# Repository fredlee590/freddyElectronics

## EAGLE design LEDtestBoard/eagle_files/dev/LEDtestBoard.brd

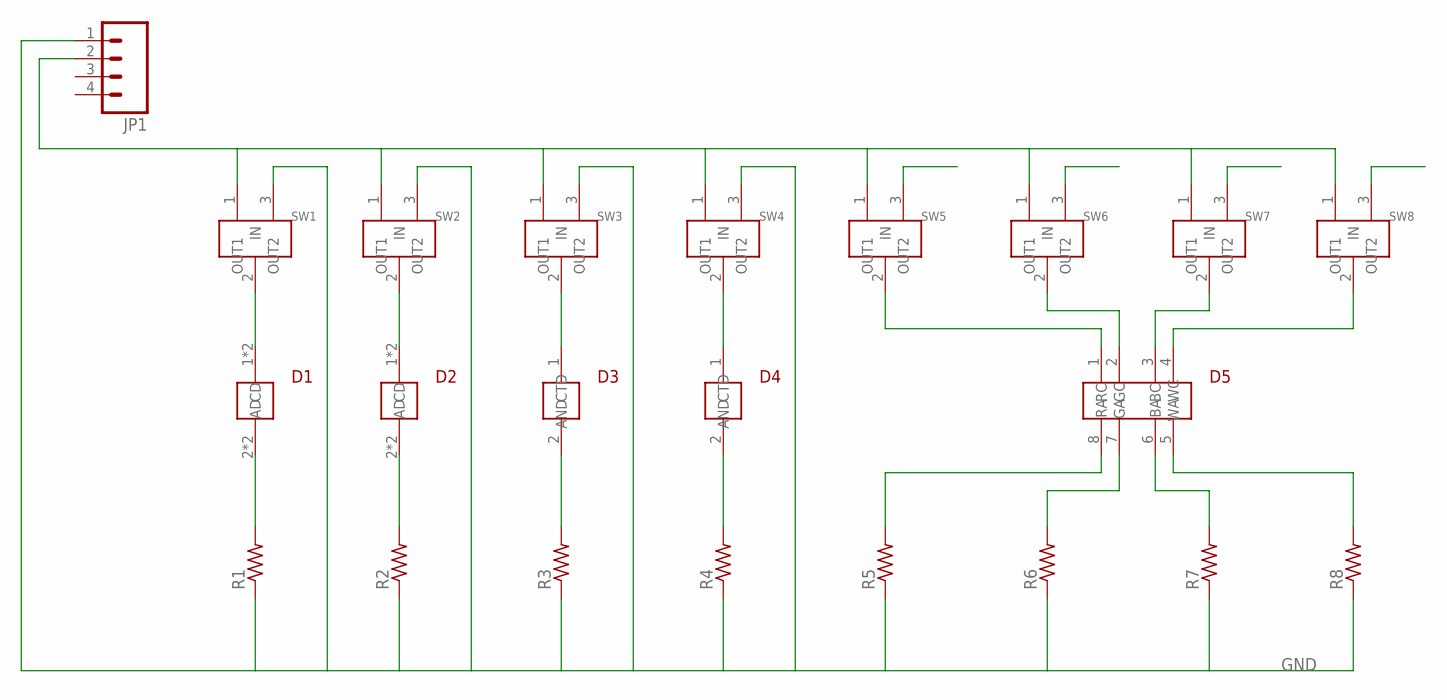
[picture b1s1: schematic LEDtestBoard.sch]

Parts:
D1, D2: SZA05A0A
D3, D4: LACN5MFBGB241Z; 2-SMD-LED-NO-EXP
D5: XLAMP_COLOR; 8-SMD-LED
JP1: M04PTH; 1X04
R1, R2, R3, R4, R5, R6, R7, R8: R-US_R0603; R0603
SW1, SW2, SW3, SW4, SW5, SW6, SW7, SW8: PCM12SMTR

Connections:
GND: JP1.1, R1.1, R2.1, R3.1, R4.1, R5.1, R6.1, R7.1, R8.1, SW1.3 (OUT2), SW2.3 (OUT2), SW3.3 (OUT2), SW4.3 (OUT2), SW5.3 (OUT2), SW6.3 (OUT2), SW7.3 (OUT2), SW8.3 (OUT2)
unnamed: JP1.2, SW1.1 (OUT1), SW2.1 (OUT1), SW3.1 (OUT1), SW4.1 (OUT1), SW5.1 (OUT1), SW6.1 (OUT1), SW7.1 (OUT1), SW8.1 (OUT1)
unnamed: D1.2 (CD), D1.12 (CD), R1.2
unnamed: D1.1 (AD), D1.11 (AD), SW1.2 (IN)
unnamed: D2.1 (AD), D2.11 (AD), SW2.2 (IN)
unnamed: D2.2 (CD), D2.12 (CD), R2.2
unnamed: D3.2 (CTD), R3.2
unnamed: D3.1 (AND), SW3.2 (IN)
unnamed: D4.1 (AND), SW4.2 (IN)
unnamed: D4.2 (CTD), R4.2
unnamed: D5.1 (RA), SW5.2 (IN)
unnamed: D5.2 (GA), SW6.2 (IN)
unnamed: D5.3 (BA), SW7.2 (IN)
unnamed: D5.4 (WA), SW8.2 (IN)
unnamed: D5.8 (RC), R5.2
unnamed: D5.7 (GC), R6.2
unnamed: D5.6 (BC), R7.2
unnamed: D5.5 (WC), R8.2

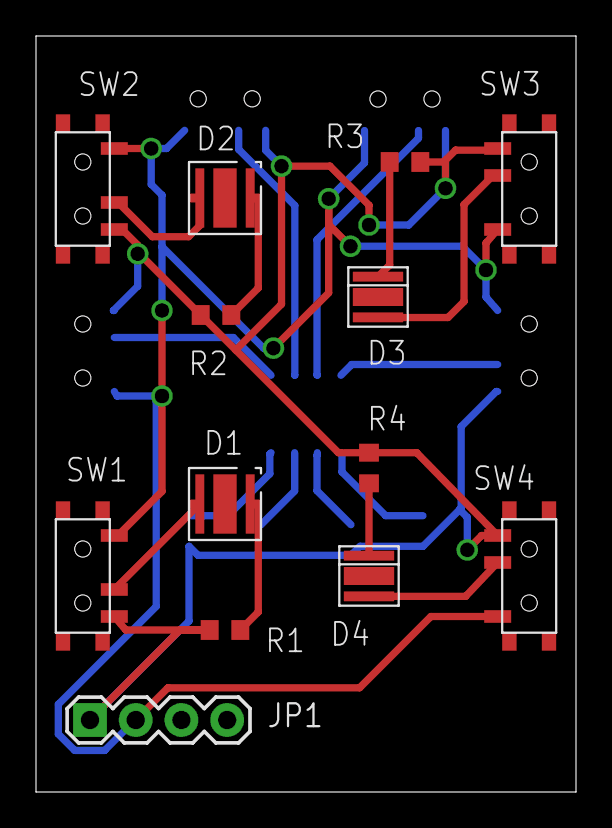
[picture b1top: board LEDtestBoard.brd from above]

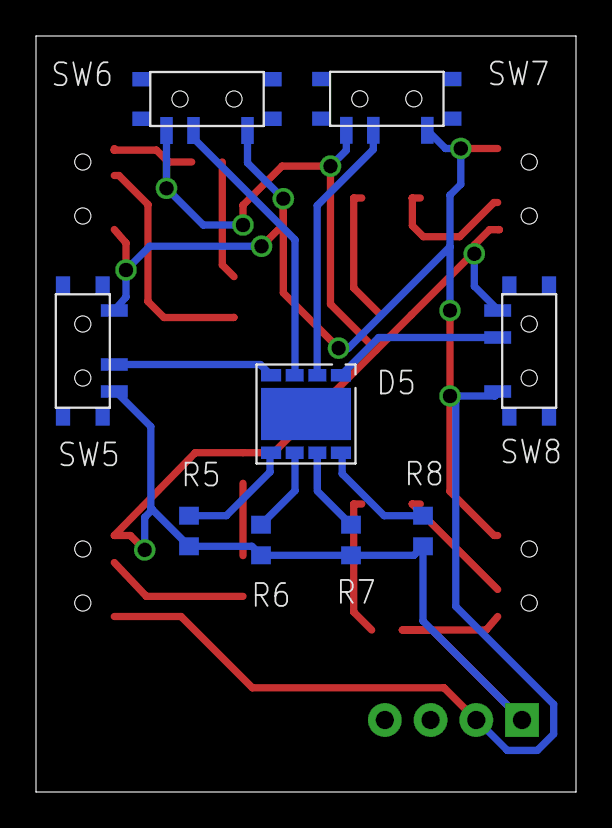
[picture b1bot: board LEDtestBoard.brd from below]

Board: 2 copper layers, 30.0 x 42.0 mm, 22 parts (9 on the bottom side), 18 nets.

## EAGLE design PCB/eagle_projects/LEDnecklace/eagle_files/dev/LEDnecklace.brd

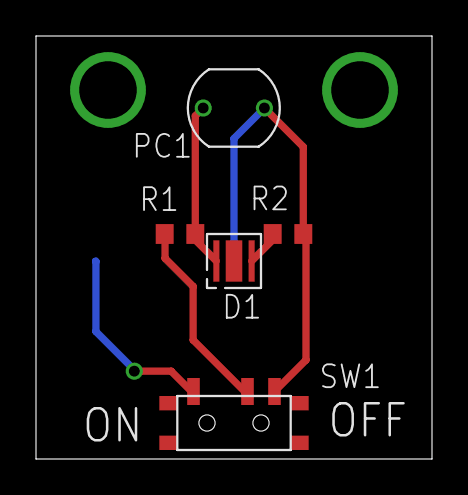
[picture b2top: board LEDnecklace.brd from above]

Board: 2 copper layers, 22.0 x 23.5 mm, 6 parts (1 on the bottom side), 5 nets.

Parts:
D1: XLAMP_XBD
P1: CR1220; CR1220/1225
PC1: PHOTOCELL_CERAMIC
R1, R2: R0603
SW1: PCM12SMTR

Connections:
unnamed: R1.2, SW1.2
unnamed: P1.GND, PC1.2, R2.1, SW1.3
unnamed: P1.VCC1, SW1.1
unnamed: D1.AD, PC1.1, R1.1
unnamed: D1.CD, R2.2

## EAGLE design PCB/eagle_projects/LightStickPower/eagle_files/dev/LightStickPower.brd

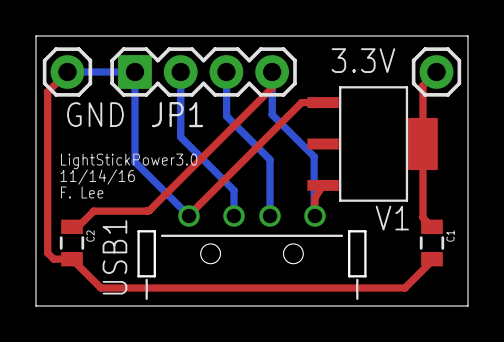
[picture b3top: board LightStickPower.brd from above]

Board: 2 copper layers, 24.0 x 15.0 mm, 7 parts (0 on the bottom side), 5 nets.

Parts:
3.3V: 1X01
C1, C2: 0805
GND: 1X01
JP1: 1X04
USB1: USB_A_932
V1: VOLTAGE_REGULATOR_AP2114H; SOT-223

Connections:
unnamed: C2.1, JP1.4, USB1.VCC, V1.VIN
unnamed: JP1.3, USB1.D-
unnamed: JP1.2, USB1.D+
unnamed: C1.2, C2.2, GND.1, JP1.1, USB1.GND, V1.GND
unnamed: 3.3V.1, C1.1, V1.VOUT2

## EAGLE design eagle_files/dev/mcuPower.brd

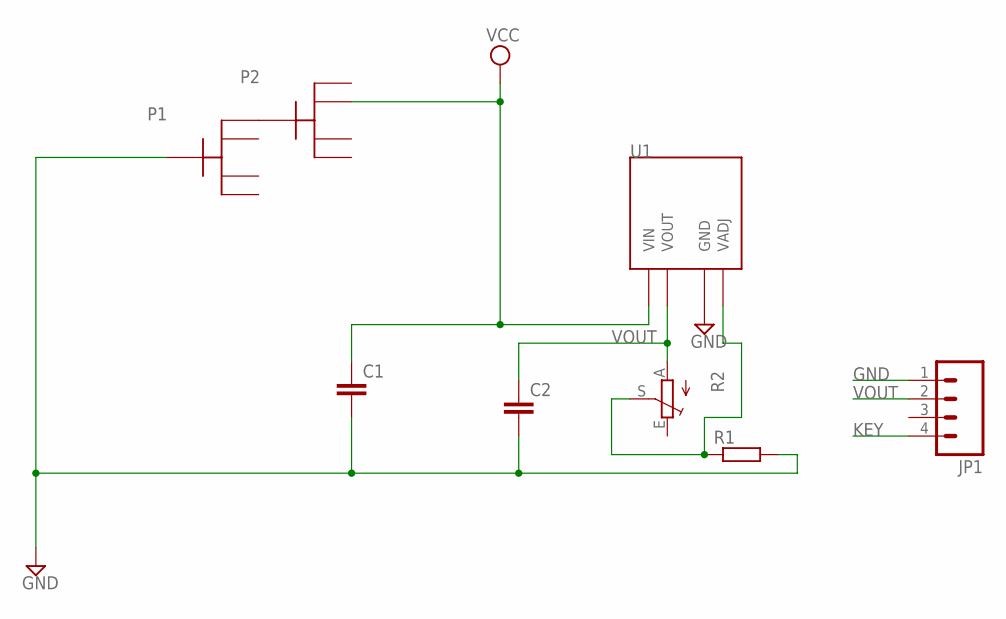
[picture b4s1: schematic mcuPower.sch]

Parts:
C1, C2: C-EUC0805; C0805
JP1: M04PTH; 1X04
P1, P2: CR2032; CR2032/2025
R1: R-EU_R0805; R0805
R2: TRIM_EU-B25P; B25P
U1: PQ070XF01SZH; TO220-4

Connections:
GND: C1.2, C2.2, JP1.1, P1.GND, R1.2, U1.GND
KEY: JP1.4
unnamed: P1.VCC_1, P2.GND
unnamed: R1.1, R2.S, U1.VADJ
VCC: C1.1, P2.VCC_2, U1.VIN
VOUT: C2.1, JP1.2, R2.A, U1.VOUT

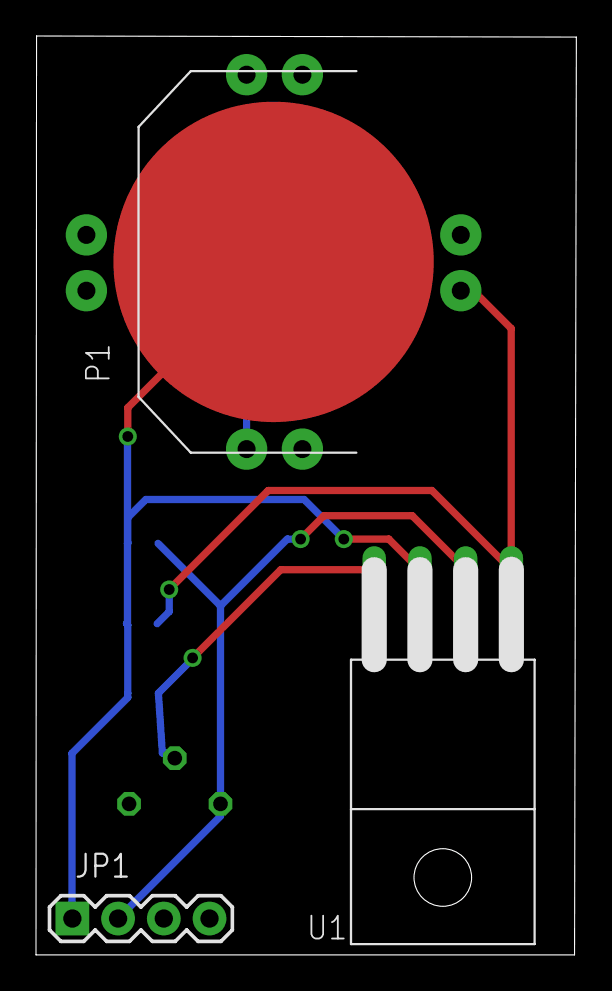
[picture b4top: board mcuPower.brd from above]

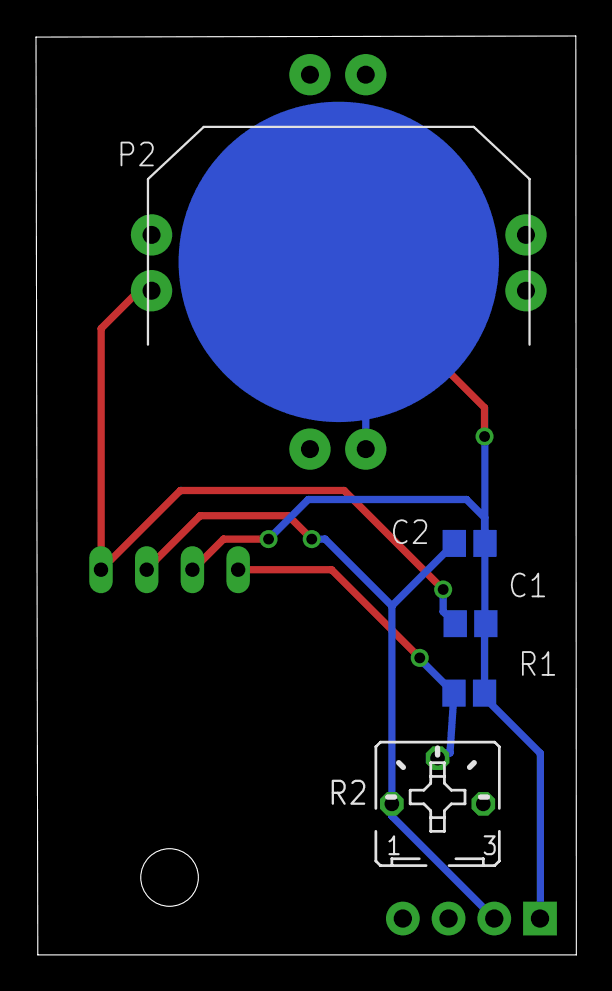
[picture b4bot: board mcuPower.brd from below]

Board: 2 copper layers, 30.0 x 51.0 mm, 8 parts (5 on the bottom side), 5 nets.

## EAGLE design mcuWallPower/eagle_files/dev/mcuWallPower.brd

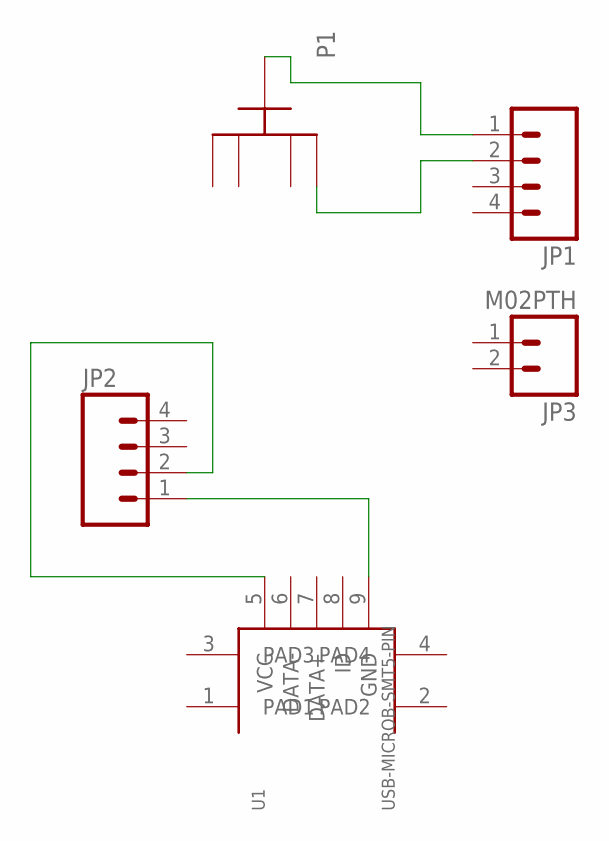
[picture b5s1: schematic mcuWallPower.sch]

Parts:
JP1, JP2: M04PTH; 1X04
JP3: M02PTH; 1X02
P1: CR2032; CR2032/2025
U1: USB-MICROB-SMT5-PIN; USB-MICROB-SMT

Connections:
unnamed: JP1.2, P1.VCC_1
unnamed: JP1.1, P1.GND
unnamed: JP2.1, U1.9 (GND)
unnamed: JP2.2, U1.5 (VCC)

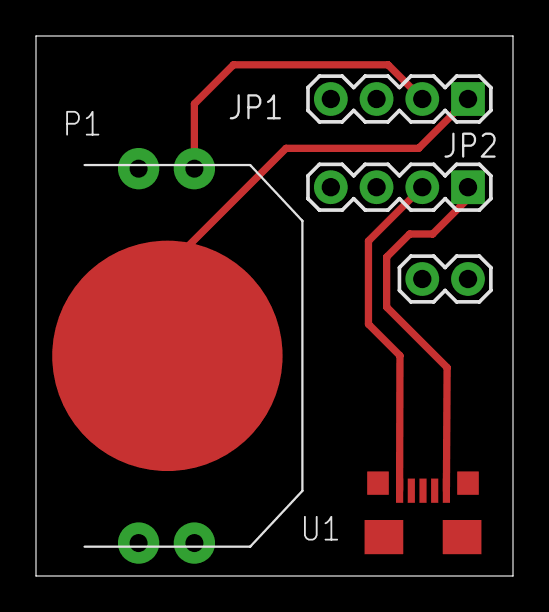
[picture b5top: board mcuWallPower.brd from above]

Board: 2 copper layers, 26.5 x 30.0 mm, 5 parts (0 on the bottom side), 4 nets.

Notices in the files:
parts and their libraries:
SparkFun-Connectors: Licensing: CC v3.0 Share-Alike You are welcome to use this library for commercial purposes.
SparkFun-Connectors: Licensing: Creative Commons ShareAlike 4.0 International - https://creativecommons.org/licenses/by-sa/4.0
